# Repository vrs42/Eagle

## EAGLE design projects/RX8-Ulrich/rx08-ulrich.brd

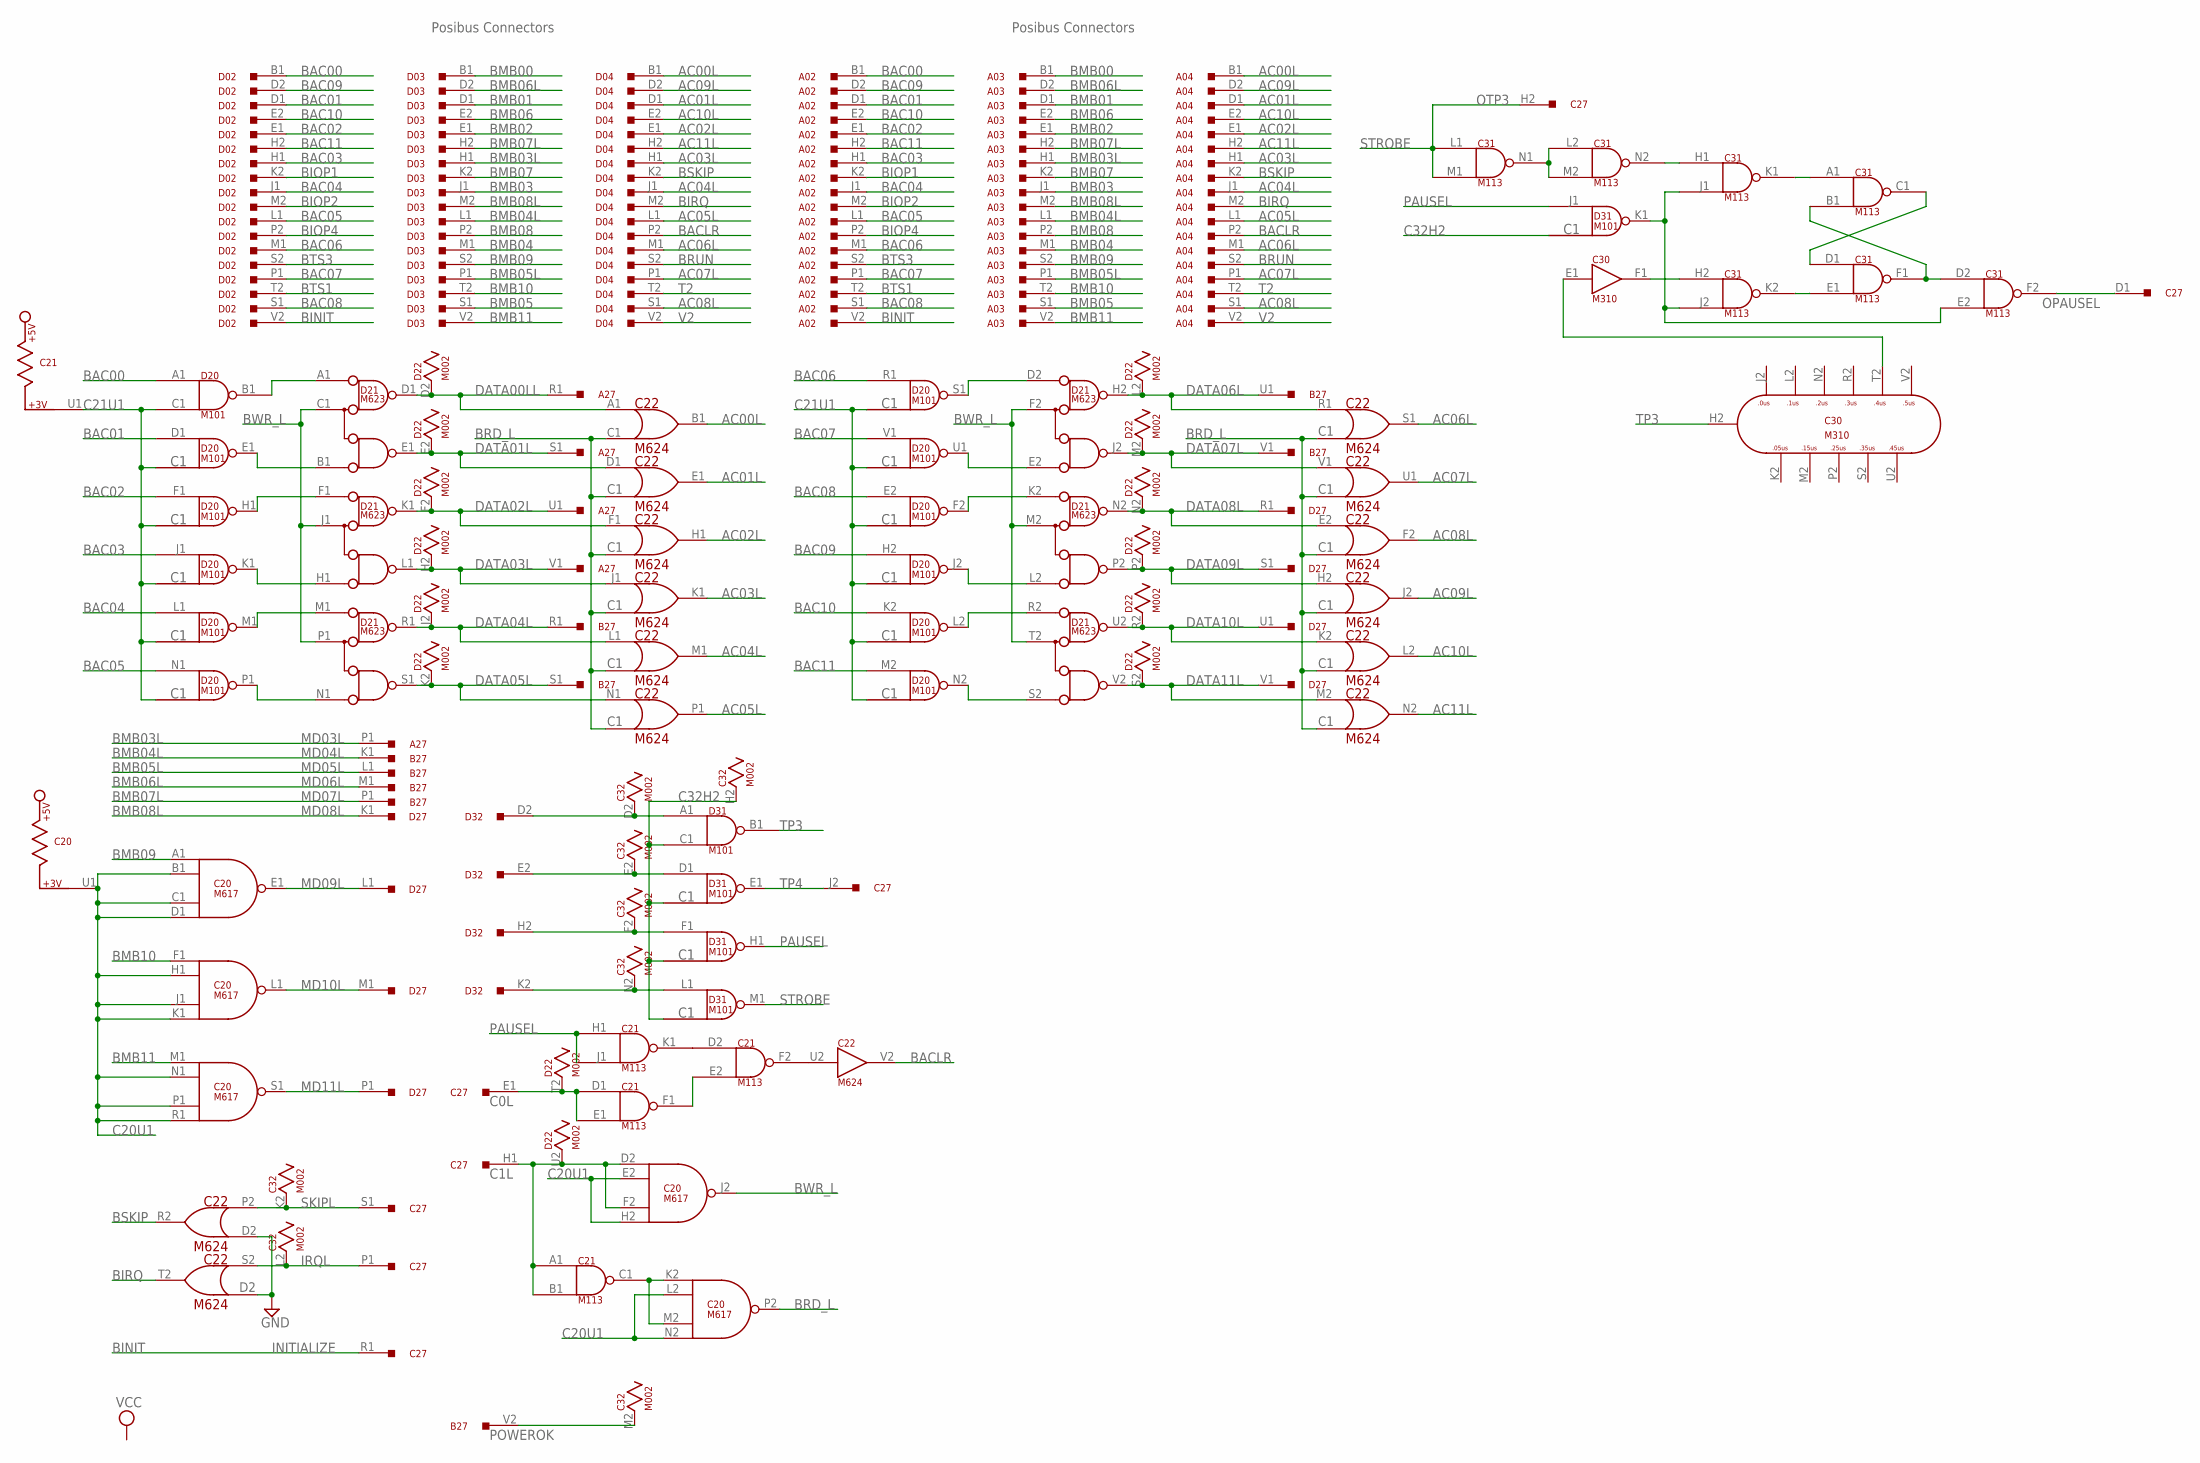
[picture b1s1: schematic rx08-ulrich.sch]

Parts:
A02, A03, A04: M903; H807
A27: M916; H807
B27: M916; H807
C20: M617; H807
C21, C31: M113; H807
C22: M624; H807
C27: M916; H807
C30: M310; H807
C32: M002; H807
D02, D03, D04, D32: M903; H807
D20, D31: M101; H807
D21: M623; H807
D22: M002; H807
D27: M916; H807

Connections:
AC00L: A04.B1, C22.B1 (OUT), D04.B1
AC01L: A04.D1, C22.E1 (OUT), D04.D1
AC02L: A04.E1, C22.H1 (OUT), D04.E1
AC03L: A04.H1, C22.K1 (OUT), D04.H1
AC04L: A04.J1, C22.M1 (OUT), D04.J1
AC05L: A04.L1, C22.P1 (OUT), D04.L1
AC06L: A04.M1, C22.S1 (OUT), D04.M1
AC07L: A04.P1, C22.U1 (OUT), D04.P1
AC08L: A04.S1, C22.F2 (OUT), D04.S1
AC09L: A04.D2, C22.J2 (OUT), D04.D2
AC10L: A04.E2, C22.L2 (OUT), D04.E2
AC11L: A04.H2, C22.N2 (OUT), D04.H2
BAC00: A02.B1, D02.B1, D20.A1 (IN1)
BAC01: A02.D1, D02.D1, D20.D1 (IN)
BAC02: A02.E1, D02.E1, D20.F1 (IN)
BAC03: A02.H1, D02.H1, D20.J1 (IN)
BAC04: A02.J1, D02.J1, D20.L1 (IN)
BAC05: A02.L1, D02.L1, D20.N1 (IN)
BAC06: A02.M1, D02.M1, D20.R1 (IN)
BAC07: A02.P1, D02.P1, D20.V1 (IN)
BAC08: A02.S1, D02.S1, D20.E2 (IN)
BAC09: A02.D2, D02.D2, D20.H2 (IN)
BAC10: A02.E2, D02.E2, D20.K2 (IN)
BAC11: A02.H2, D02.H2, D20.M2 (IN)
BACLR: A04.P2, C22.V2 (OUT), D04.P2
BINIT: A02.V2, C27.R1, D02.V2
BIOP1: A02.K2, D02.K2
BIOP2: A02.M2, D02.M2
BIOP4: A02.P2, D02.P2
BIRQ: A04.M2, C22.T2 (OUT), D04.M2
BMB00: A03.B1, D03.B1
BMB01: A03.D1, D03.D1
BMB02: A03.E1, D03.E1
BMB03: A03.J1, D03.J1
BMB03L: A03.H1, A27.P1, D03.H1
BMB04: A03.M1, D03.M1
BMB04L: A03.L1, B27.K1, D03.L1
BMB05: A03.S1, D03.S1
BMB05L: A03.P1, B27.L1, D03.P1
BMB06: A03.E2, D03.E2
BMB06L: A03.D2, B27.M1, D03.D2
BMB07: A03.K2, D03.K2
BMB07L: A03.H2, B27.P1, D03.H2
BMB08: A03.P2, D03.P2
BMB08L: A03.M2, D03.M2, D27.K1
BMB09: A03.S2, C20.A1 (IN1), D03.S2
BMB10: A03.T2, C20.F1 (IN1), D03.T2
BMB11: A03.V2, C20.M1 (IN1), D03.V2
BRD_L: C20.P2 (OUT), C22.C1 (IN2)
BRUN: A04.S2, D04.S2
BSKIP: A04.K2, C22.R2 (OUT), D04.K2
BTS1: A02.T2, D02.T2
BTS3: A02.S2, D02.S2
BWR_L: C20.J2 (OUT), D21.C1 (C), D21.F2 (C), D21.J1 (C), D21.M2 (C), D21.P1 (C), D21.T2 (C)
C0L: C21.D1 (IN1), C21.E1 (IN2), C27.E1, D22.T2
C1L: C20.D2 (IN1), C20.F2 (IN3), C21.A1 (IN1), C21.B1 (IN2), C27.H1, D22.U2
C20U1: C20.B1 (IN2), C20.C1 (IN3), C20.D1 (IN4), C20.E2 (IN2), C20.H1 (IN2), C20.H2 (IN4), C20.J1 (IN3), C20.K1 (IN4), C20.L2 (IN2), C20.N1 (IN2), C20.N2 (IN4), C20.P1 (IN3), C20.R1 (IN4), C20.U1
C21U1: C21.U1, D20.C1 (IN2)
C32H2: C32.H2, D31.C1 (IN2)
DATA00LL: A27.R1, C22.A1 (IN1), D21.D1 (D), D22.D2
DATA01L: A27.S1, C22.D1 (IN), D21.E1 (E), D22.E2
DATA02L: A27.U1, C22.F1 (IN), D21.K1 (D), D22.F2
DATA03L: A27.V1, C22.J1 (IN), D21.L1 (E), D22.H2
DATA04L: B27.R1, C22.L1 (IN), D21.R1 (D), D22.J2
DATA05L: B27.S1, C22.N1 (IN), D21.S1 (E), D22.K2
DATA06L: B27.U1, C22.R1 (IN), D21.H2 (D), D22.L2
DATA07L: B27.V1, C22.V1 (IN), D21.J2 (E), D22.M2
DATA08L: C22.E2 (IN), D21.N2 (D), D22.N2, D27.R1
DATA09L: C22.H2 (IN), D21.P2 (E), D22.P2, D27.S1
DATA10L: C22.K2 (IN), D21.U2 (D), D22.R2, D27.U1
DATA11L: C22.M2 (IN), D21.V2 (E), D22.S2, D27.V1
GND: A02.A1 (GND), A02.C1 (GND), A02.C2 (GND), A02.F1 (GND), A02.F2 (GND), A02.J2 (GND), A02.K1 (GND), A02.L2 (GND), A02.N1 (GND), A02.N2 (GND), A02.R1 (GND), A02.R2 (GND), A02.T1 (GND), A02.U2 (GND), A03.A1 (GND), A03.C1 (GND), A03.C2 (GND), A03.F1 (GND), A03.F2 (GND), A03.J2 (GND), A03.K1 (GND), A03.L2 (GND), A03.N1 (GND), A03.N2 (GND), A03.R1 (GND), A03.R2 (GND), A03.T1 (GND), A03.U2 (GND), A04.A1 (GND), A04.C1 (GND), A04.C2 (GND), A04.F1 (GND), A04.F2 (GND), A04.J2 (GND), A04.K1 (GND), A04.L2 (GND), A04.N1 (GND), A04.N2 (GND), A04.R1 (GND), A04.R2 (GND), A04.T1 (GND), A04.U2 (GND), C20.C2 (GND), C20.T1 (GND), C21.C2 (GND), C21.T1 (GND), C22.C2 (GND), C22.D2 (IN2), C22.T1 (GND), C30.C2 (GND), C30.T1 (GND), C31.C2 (GND), C31.T1 (GND), C32.C2 (GND), D02.A1 (GND), D02.C1 (GND), D02.C2 (GND), D02.F1 (GND), D02.F2 (GND), D02.J2 (GND), D02.K1 (GND), D02.L2 (GND), D02.N1 (GND), D02.N2 (GND), D02.R1 (GND), D02.R2 (GND), D02.T1 (GND), D02.U2 (GND), D03.A1 (GND), D03.C1 (GND), D03.C2 (GND), D03.F1 (GND), D03.F2 (GND), D03.J2 (GND), D03.K1 (GND), D03.L2 (GND), D03.N1 (GND), D03.N2 (GND), D03.R1 (GND), D03.R2 (GND), D03.T1 (GND), D03.U2 (GND), D04.A1 (GND), D04.C1 (GND), D04.C2 (GND), D04.F1 (GND), D04.F2 (GND), D04.J2 (GND), D04.K1 (GND), D04.L2 (GND), D04.N1 (GND), D04.N2 (GND), D04.R1 (GND), D04.R2 (GND), D04.T1 (GND), D04.U2 (GND), D20.C2 (GND), D20.T1 (GND), D21.C2 (GND), D21.T1 (GND), D21.U1 (GND), D21.V1 (GND), D22.C2 (GND), D31.C2 (GND), D31.T1 (GND), D32.A1 (GND), D32.C1 (GND), D32.C2 (GND), D32.F1 (GND), D32.F2 (GND), D32.J2 (GND), D32.K1 (GND), D32.L2 (GND), D32.N1 (GND), D32.N2 (GND), D32.R1 (GND), D32.R2 (GND), D32.T1 (GND), D32.U2 (GND)
IRQL: C22.S2 (IN), C27.P1, C32.L2
MD09L: C20.E1 (OUT), D27.L1
MD10L: C20.L1 (OUT), D27.M1
MD11L: C20.S1 (OUT), D27.P1
unnamed: D20.B1 (OUT), D21.A1 (A)
unnamed: D20.E1 (OUT), D21.B1 (B)
unnamed: D20.H1 (OUT), D21.F1 (A)
unnamed: D20.K1 (OUT), D21.H1 (B)
unnamed: D20.P1 (OUT), D21.N1 (B)
unnamed: D20.M1 (OUT), D21.M1 (A)
unnamed: C20.K2 (IN1), C20.M2 (IN3), C21.C1 (OUT)
unnamed: D20.N2 (OUT), D21.S2 (B)
unnamed: C32.D2, D31.A1 (IN1), D32.D2
unnamed: D20.J2 (OUT), D21.L2 (B)
unnamed: D20.U1 (OUT), D21.E2 (B)
unnamed: D20.S1 (OUT), D21.D2 (A)
unnamed: D20.F2 (OUT), D21.K2 (A)
unnamed: D20.L2 (OUT), D21.R2 (A)
unnamed: C32.E2, D31.D1 (IN), D32.E2
unnamed: C32.F2, D31.F1 (IN), D32.H2
unnamed: C32.N2, D31.L1 (IN), D32.K2
unnamed: C31.E2 (IN2), C31.J1 (IN2), C31.J2 (IN2), D31.K1 (OUT)
unnamed: C21.E2 (IN2), C21.F1 (OUT)
unnamed: C21.D2 (IN1), C21.K1 (OUT)
unnamed: C31.C1 (OUT), C31.D1 (IN1)
unnamed: C31.B1 (IN2), C31.D2 (IN1), C31.F1 (OUT)
unnamed: C21.F2 (OUT), C22.U2 (IN)
unnamed: C30.E1 (IN), C30.T2
unnamed: C30.F1 (OUT), C31.H2 (IN1)
unnamed: C31.L2 (IN1), C31.M2 (IN2), C31.N1 (OUT)
unnamed: C31.H1 (IN1), C31.N2 (OUT)
unnamed: C31.A1 (IN1), C31.K1 (OUT)
unnamed: C31.E1 (IN2), C31.K2 (OUT)
OPAUSEL: C27.D1, C31.F2 (OUT)
PAUSEL: C21.H1 (IN1), C21.J1 (IN2), D31.H1 (OUT), D31.J1 (IN)
POWEROK: B27.V2, C32.M2
SKIPL: C22.P2 (IN1), C27.S1, C32.K2
STROBE: C27.H2, C31.L1 (IN1), C31.M1 (IN2), D31.M1 (OUT)
T2: A04.T2, D04.T2
TP3: C30.H2, D31.B1 (OUT)
TP4: C27.J2, D31.E1 (OUT)
V2: A04.V2, D04.V2
VCC: C20.A2 (VCC), C21.A2 (VCC), C22.A2 (VCC), C30.A2 (VCC), C31.A2 (VCC), C32.A2 (VCC), D20.A2 (VCC), D21.A2 (VCC), D22.A2 (VCC), D31.A2 (VCC)

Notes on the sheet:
Posibus Connectors
MD03L
MD04L
MD05L
MD06L
MD07L
MD08L
INITIALIZE
OTP3

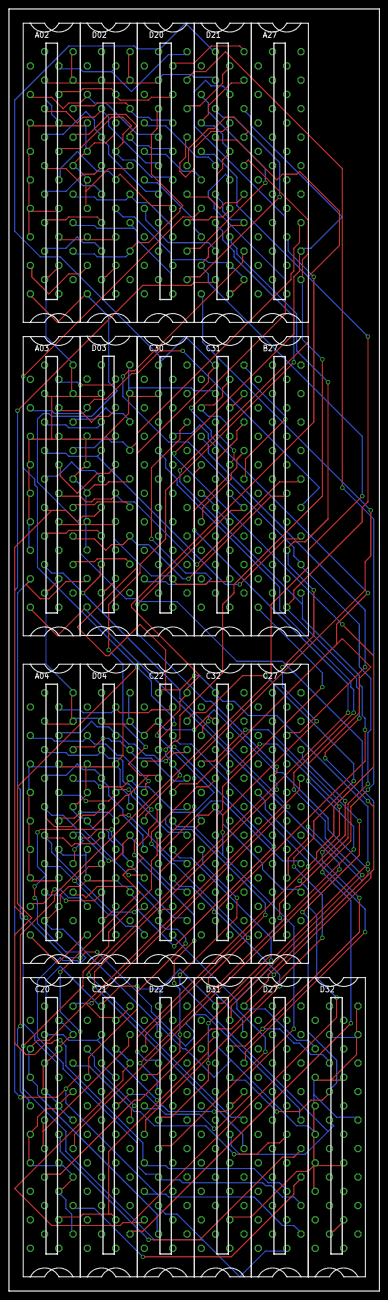
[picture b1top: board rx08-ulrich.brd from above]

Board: 2 copper layers, 82.5 x 285.8 mm, 21 parts (0 on the bottom side), 115 nets.

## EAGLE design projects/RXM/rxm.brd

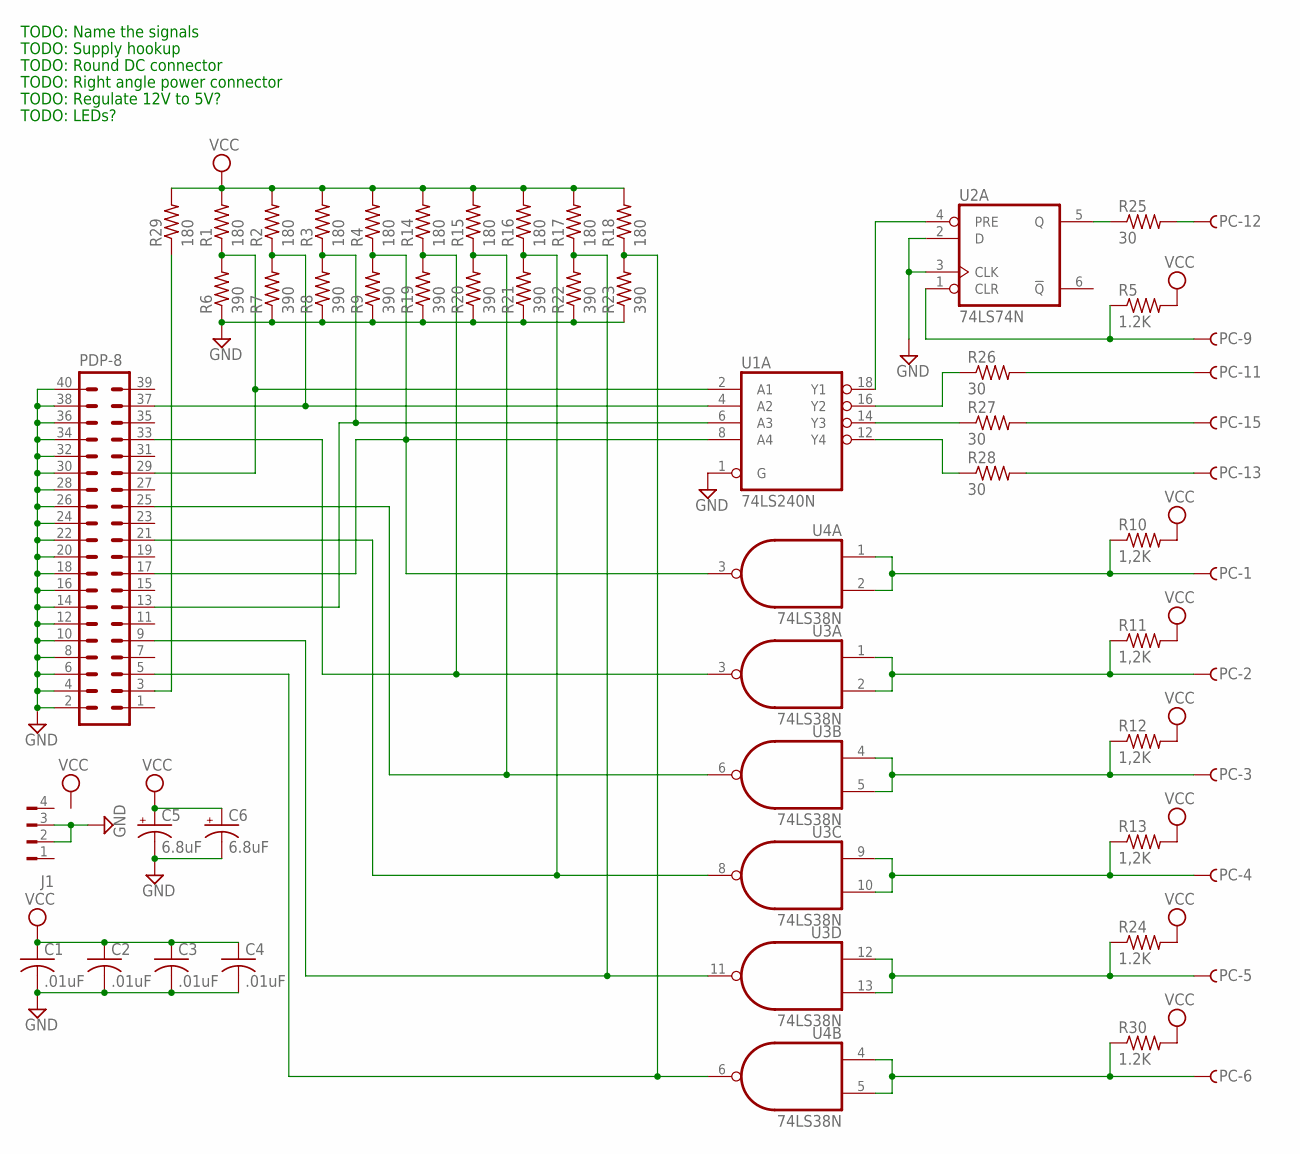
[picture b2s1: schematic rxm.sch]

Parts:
C1, C2, C3, C4: .01uF; C050-025X075
C5, C6: 6.8uF; E2,5-6E
J1: FLOPPY-4
PC: F25HS; F25H
PDP-8: 40H
R1, R2, R3, R4, R14, R15, R16, R17, R18, R29: 180; 0207/10
R5, R24, R30: 1.2K; 0207/10
R6, R7, R8, R9, R19, R20, R21, R22, R23: 390; 0207/10
R10, R11, R12, R13: 1,2K; 0207/10
R25, R26, R27, R28: 30; 0207/10
U1: 74LS240N; DIL20
U2: 74LS74N; DIL14
U3, U4: 74LS38N; DIL14

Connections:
GND: C1.2, C2.2, C3.2, C4.2, C5.-, C6.-, J1.2, J1.3, PDP-8.2, PDP-8.4, PDP-8.6, PDP-8.8, PDP-8.10, PDP-8.12, PDP-8.14, PDP-8.16, PDP-8.18, PDP-8.20, PDP-8.22, PDP-8.24, PDP-8.26, PDP-8.28, PDP-8.30, PDP-8.32, PDP-8.34, PDP-8.36, PDP-8.38, PDP-8.40, R6.1, R7.1, R8.1, R9.1, R19.1, R20.1, R21.1, R22.1, R23.1, U1.1 (G), U1.10 (GND), U2.2 (D), U2.3 (CLK), U2.7 (GND), U3.7 (GND), U4.7 (GND)
unnamed: PDP-8.29, R1.1, R6.2, U1.2 (A1)
unnamed: PDP-8.37, R2.1, R7.2, U1.4 (A2)
unnamed: PDP-8.13, R3.1, R8.2, U1.6 (A3)
unnamed: PDP-8.17, R4.1, R9.2, U1.8 (A4), U4.3 (O)
unnamed: PDP-8.33, R14.1, R19.2, U3.3 (O)
unnamed: PDP-8.25, R15.1, R20.2, U3.6 (O)
unnamed: PDP-8.21, R16.1, R21.2, U3.8 (O)
unnamed: PDP-8.9, R17.1, R22.2, U3.11 (O)
unnamed: PDP-8.5, R18.1, R23.2, U4.6 (O)
unnamed: PC.12, R25.2
unnamed: PC.11, R26.2
unnamed: PC.15, R27.2
unnamed: PC.13, R28.2
unnamed: PDP-8.3, R29.1
unnamed: PC.1, R10.1, U4.1 (I0), U4.2 (I1)
unnamed: PC.2, R11.1, U3.1 (I0), U3.2 (I1)
unnamed: PC.3, R12.1, U3.4 (I0), U3.5 (I1)
unnamed: PC.4, R13.1, U3.9 (I0), U3.10 (I1)
unnamed: PC.6, R30.1, U4.4 (I0), U4.5 (I1)
unnamed: PC.5, R24.1, U3.12 (I0), U3.13 (I1)
unnamed: U1.18 (Y1), U2.4 (PRE)
unnamed: PC.9, R5.1, U2.1 (CLR)
unnamed: R25.1, U2.5 (Q)
unnamed: R28.1, U1.12 (Y4)
unnamed: R27.1, U1.14 (Y3)
unnamed: R26.1, U1.16 (Y2)
VCC: C1.1, C2.1, C3.1, C4.1, C5.+, C6.+, R1.2, R2.2, R3.2, R4.2, R5.2, R10.2, R11.2, R12.2, R13.2, R14.2, R15.2, R16.2, R17.2, R18.2, R24.2, R29.2, R30.2, U1.20 (VCC), U2.14 (VCC), U3.14 (VCC), U4.14 (VCC)

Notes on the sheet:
TODO: Supply hookup
TODO: Round DC connector
TODO: Right angle power connector
TODO: Regulate 12V to 5V?
TODO: Name the signals
TODO: LEDs?

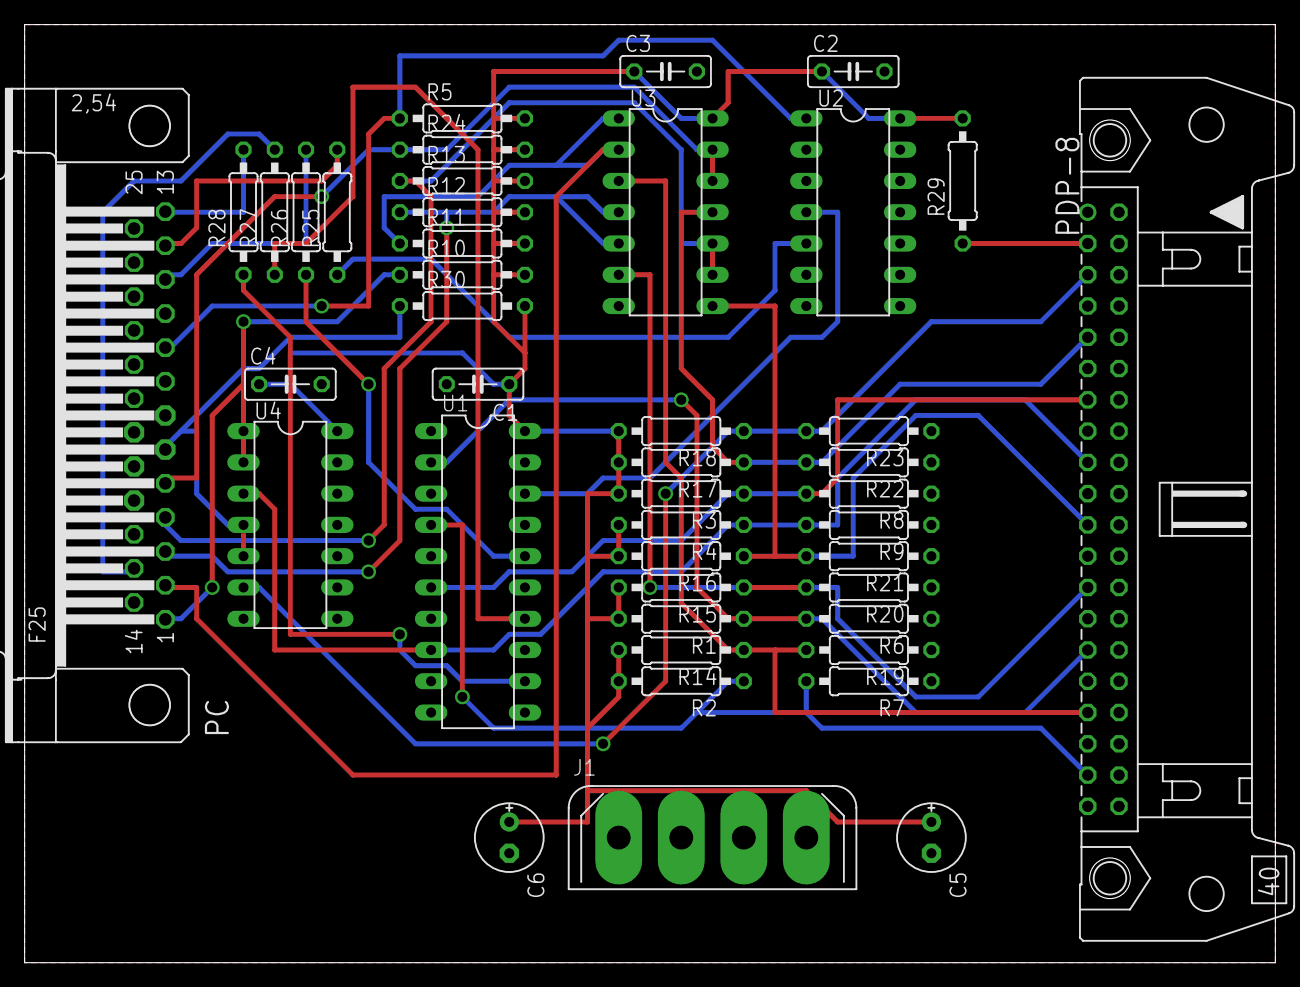
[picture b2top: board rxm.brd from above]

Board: 2 copper layers, 101.6 x 76.2 mm, 43 parts (0 on the bottom side), 28 nets.

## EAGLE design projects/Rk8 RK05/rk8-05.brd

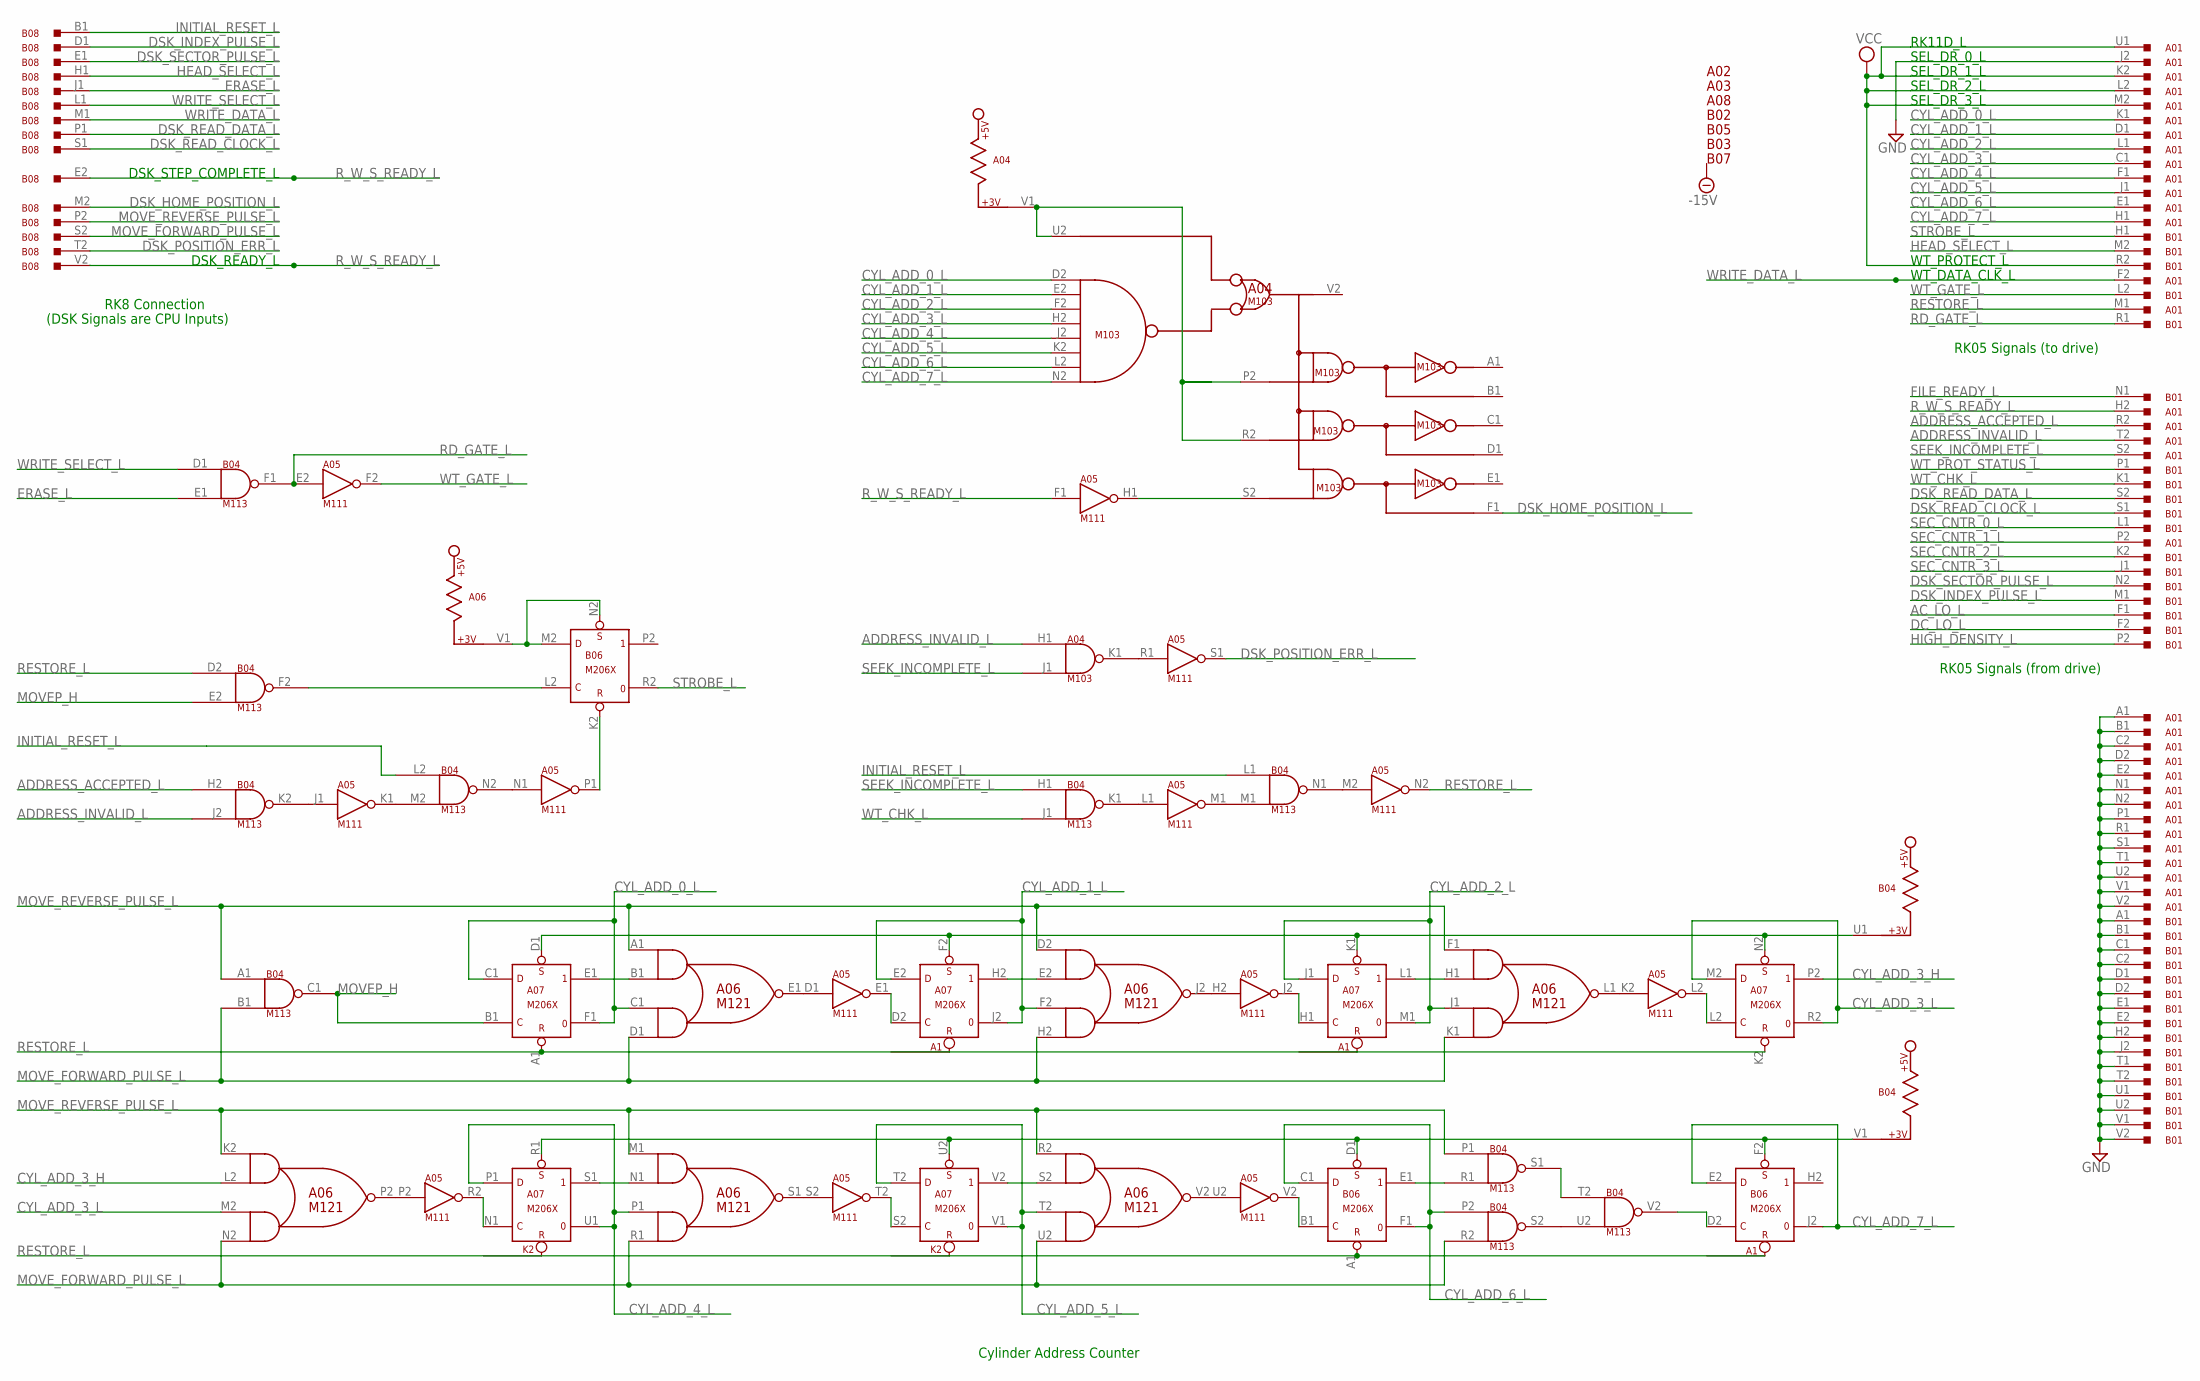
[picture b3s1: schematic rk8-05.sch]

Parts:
A01: M916; H807
A02, A03, A08: EMPTY; H807
A04: M103; H807
A05: M111; H807
A06: M121; H807
A07: M206X; H807
B01: M916; H807
B02, B03, B05, B07: EMPTY; H807
B04: M113; H807
B06: M206X; H807
B08: M903; H807

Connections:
-15V: A02.B2 (-15V), A03.B2 (-15V), A08.B2 (-15V), B02.B2 (-15V), B03.B2 (-15V), B05.B2 (-15V), B07.B2 (-15V)
AC_LO_L: B01.F1
ADDRESS_ACCEPTED_L: A01.R2, B04.H2 (IN1)
ADDRESS_INVALID_L: A01.T2, A04.H1 (IN1), B04.J2 (IN2)
CYL_ADD_0_L: A01.K1, A04.D2, A06.C1 (IN2A), A07.C1 (D), A07.F1 (0)
CYL_ADD_1_L: A01.D1, A04.E2, A06.F2 (IN2A), A07.E2 (D), A07.J2 (0)
CYL_ADD_2_L: A01.L1, A04.F2, A06.J1 (IN2A), A07.J1 (D), A07.M1 (0)
CYL_ADD_3_H: A06.L2 (IN1B), A07.P2 (1)
CYL_ADD_3_L: A01.C1, A04.H2, A06.M2 (IN2A), A07.M2 (D), A07.R2 (0)
CYL_ADD_4_L: A01.F1, A04.J2, A06.P1 (IN2A), A07.P1 (D), A07.U1 (0)
CYL_ADD_5_L: A01.J1, A04.K2, A06.T2 (IN2A), A07.T2 (D), A07.V1 (0)
CYL_ADD_6_L: A01.E1, A04.L2, B04.P2 (IN1), B06.C1 (D), B06.F1 (0)
CYL_ADD_7_L: A01.H1, A04.N2, B06.E2 (D), B06.J2 (0)
DC_LO_L: B01.F2
DSK_HOME_POSITION_L: A04.F1, B08.M2
DSK_INDEX_PULSE_L: B01.M1, B08.D1
DSK_POSITION_ERR_L: A05.S1 (OUT), B08.T2
DSK_READ_CLOCK_L: B01.S1, B08.S1
DSK_READ_DATA_L: B01.S2, B08.P1
DSK_SECTOR_PULSE_L: B01.N2, B08.E1
ERASE_L: B04.E1 (IN2), B08.J1
FILE_READY_L: B01.N1
GND: A01.A1, A01.B1, A01.C2, A01.D2, A01.E2, A01.J2, A01.N1, A01.N2, A01.P1, A01.R1, A01.S1, A01.T1, A01.U2, A01.V1, A01.V2, A02.C2 (GND), A03.C2 (GND), A04.C2 (GND), A04.T1 (GND), A05.C2 (GND), A05.T1 (GND), A06.C2 (GND), A06.T1 (GND), A07.C2 (GND), A07.T1 (GND), A08.C2 (GND), B01.A1, B01.B1, B01.C1, B01.C2, B01.D1, B01.D2, B01.E1, B01.E2, B01.H2, B01.J2, B01.T1, B01.T2, B01.U1, B01.U2, B01.V1, B01.V2, B02.C2 (GND), B03.C2 (GND), B04.C2 (GND), B04.T1 (GND), B05.C2 (GND), B06.C2 (GND), B06.T1 (GND), B07.C2 (GND), B08.A1 (GND), B08.C1 (GND), B08.C2 (GND), B08.F1 (GND), B08.F2 (GND), B08.J2 (GND), B08.K1 (GND), B08.L2 (GND), B08.N1 (GND), B08.N2 (GND), B08.R1 (GND), B08.R2 (GND), B08.T1 (GND), B08.U2 (GND)
HEAD_SELECT_L: B01.M2, B08.H1
HIGH_DENSITY_L: B01.P2
INITIAL_RESET_L: B04.L1 (IN1), B04.L2 (IN1), B08.B1
MOVEP_H: A07.B1 (C), B04.C1 (OUT), B04.E2 (IN2)
MOVE_FORWARD_PULSE_L: A06.D1 (IN2B), A06.H2 (IN2B), A06.K1 (IN2B), A06.N2 (IN2B), A06.R1 (IN2B), A06.U2 (IN2B), B04.B1 (IN2), B04.R2 (IN2), B08.S2
MOVE_REVERSE_PULSE_L: A06.A1 (IN1A), A06.D2 (IN1A), A06.F1 (IN1A), A06.K2 (IN1A), A06.M1 (IN1A), A06.R2 (IN1A), B04.A1 (IN1), B04.P1 (IN1), B08.P2
unnamed: A05.P2 (IN), A06.P2 (OUT)
unnamed: A07.D1 (S), A07.F2 (S), A07.K1 (S), A07.N2 (S), B04.U1
unnamed: A07.R1 (S), A07.U2 (S), B04.V1, B06.D1 (S), B06.F2 (S)
unnamed: A06.B1 (IN1B), A07.E1 (1)
unnamed: A05.E1 (OUT), A07.D2 (C)
unnamed: A06.E2 (IN1B), A07.H2 (1)
unnamed: A05.J2 (OUT), A07.H1 (C)
unnamed: A05.R2 (OUT), A07.N1 (C)
unnamed: A06.H1 (IN1B), A07.L1 (1)
unnamed: A05.S2 (IN), A06.S1 (OUT)
unnamed: A05.L2 (OUT), A07.L2 (C)
unnamed: A05.T2 (OUT), A07.S2 (C)
unnamed: B04.S2 (OUT), B04.U2 (IN2)
unnamed: B04.S1 (OUT), B04.T2 (IN1)
unnamed: A05.H2 (IN), A06.J2 (OUT)
unnamed: A04.S2, A05.H1 (OUT)
unnamed: A05.D1 (IN), A06.E1 (OUT)
unnamed: A05.U2 (IN), A06.V2 (OUT)
unnamed: B04.V2 (OUT), B06.D2 (C)
unnamed: B04.R1 (IN2), B06.E1 (1)
unnamed: A05.K2 (IN), A06.L1 (OUT)
unnamed: A06.S2 (IN1B), A07.V2 (1)
unnamed: A06.N1 (IN1B), A07.S1 (1)
unnamed: B04.F2 (OUT), B06.L2 (C)
unnamed: A05.L1 (IN), B04.K1 (OUT)
unnamed: A05.M1 (OUT), B04.M1 (IN2)
unnamed: A06.V1, B06.M2 (D), B06.N2 (S)
unnamed: A04.K1 (OUT), A05.R1 (IN)
unnamed: A05.V2 (OUT), B06.B1 (C)
unnamed: A05.J1 (IN), B04.K2 (OUT)
unnamed: A05.K1 (OUT), B04.M2 (IN2)
unnamed: A05.N1 (IN), B04.N2 (OUT)
unnamed: A05.P1 (OUT), B06.K2 (R)
unnamed: A05.M2 (IN), B04.N1 (OUT)
unnamed: A04.P2, A04.R2, A04.U2, A04.V1
RD_GATE_L: A05.E2 (IN), B01.R1, B04.F1 (OUT)
RESTORE_L: A01.M1, A05.N2 (OUT), A07.A1 (R), A07.K2 (R), B04.D2 (IN1), B06.A1 (R)
R_W_S_READY_L: A01.H2, A05.F1 (IN), B08.E2, B08.V2
SEC_CNTR_0_L: B01.L1
SEC_CNTR_1_L: A01.P2
SEC_CNTR_2_L: B01.K2
SEC_CNTR_3_L: B01.J1
SEEK_INCOMPLETE_L: A01.S2, A04.J1 (IN2), B04.H1 (IN1)
STROBE_L: B01.H1, B06.R2 (0)
VCC: A01.K2, A01.L2, A01.M2, A01.U1, A02.A2 (VCC), A03.A2 (VCC), A04.A2 (VCC), A05.A2 (VCC), A06.A2 (VCC), A07.A2 (VCC), A08.A2 (VCC), B01.R2, B02.A2 (VCC), B03.A2 (VCC), B04.A2 (VCC), B05.A2 (VCC), B06.A2 (VCC), B07.A2 (VCC)
WRITE_DATA_L: A01.F2, B08.M1
WRITE_SELECT_L: B04.D1 (IN1), B08.L1
WT_CHK_L: B01.K1, B04.J1 (IN2)
WT_GATE_L: A05.F2 (OUT), B01.L2
WT_PROT_STATUS_L: B01.P1

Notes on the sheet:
RK8 Connection
(DSK Signals are CPU Inputs)
RK05 Signals (to drive)
RK05 Signals (from drive)
Cylinder Address Counter
SEL_DR_0_L
SEL_DR_1_L
SEL_DR_2_L
SEL_DR_3_L
RK11D_L
WT_PROTECT_L
WT_DATA_CLK_L
DSK_STEP_COMPLETE_L
DSK_READY_L

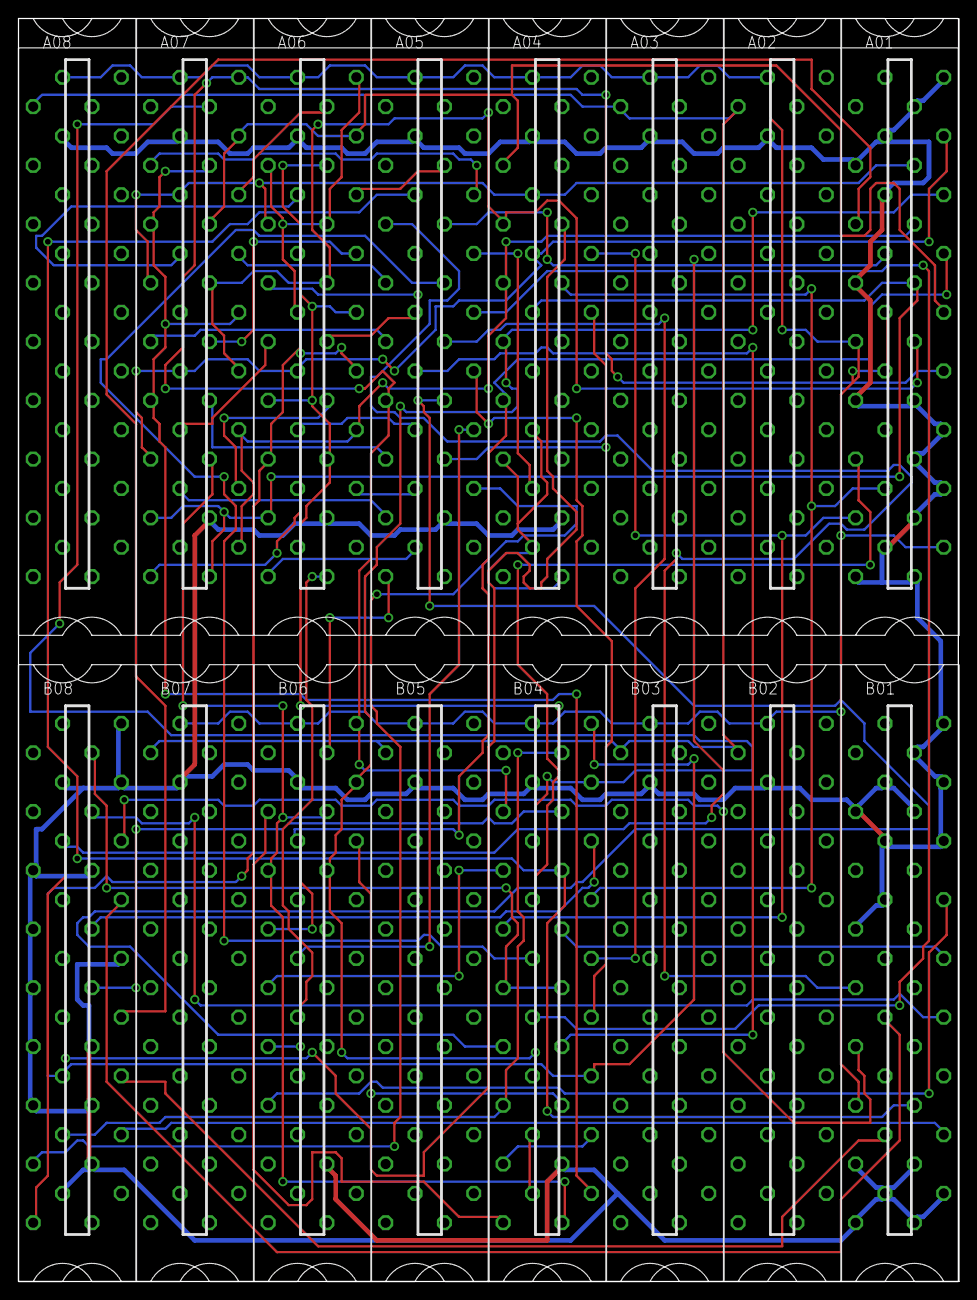
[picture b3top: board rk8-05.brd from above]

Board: 2 copper layers, 101.6 x 136.5 mm, 18 parts (0 on the bottom side), 70 nets.

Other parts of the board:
U$1, U$2: CBLOCK

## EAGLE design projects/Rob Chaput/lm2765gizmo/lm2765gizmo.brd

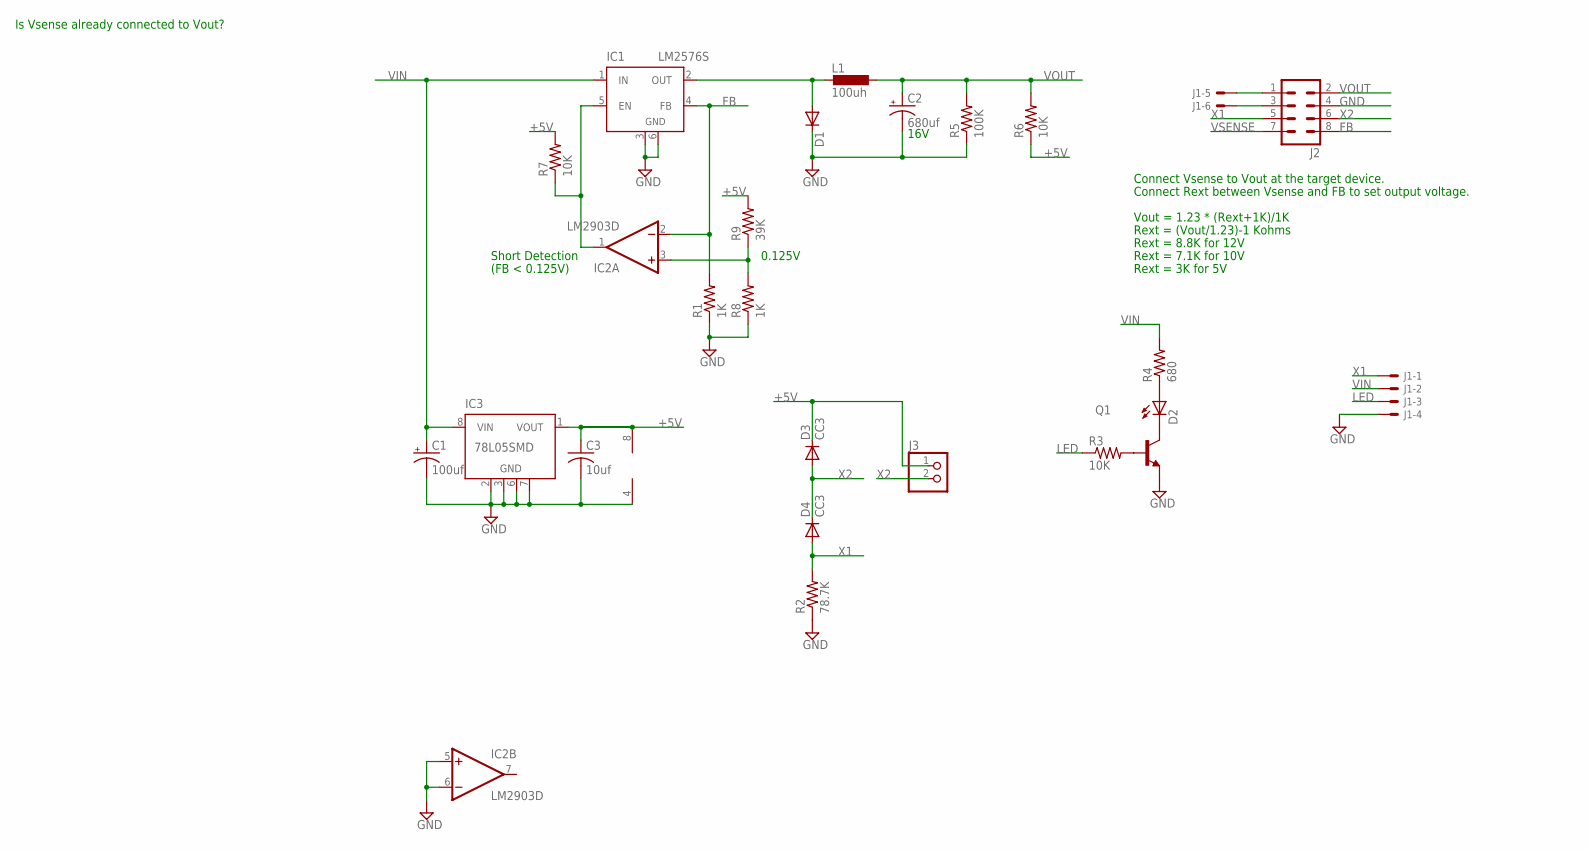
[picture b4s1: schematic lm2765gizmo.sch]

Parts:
C1: 100uf; 140CLH-0810
C2: 680uf; 140CLH-1014
C3: 10uf; C0805
D1: DIODE-SMC; SMC
D2: LEDCHIP-LED0805; CHIP-LED0805
D3, D4: CC3; SOD80C
IC1: LM2576S; TO263-5
IC2: LM2903D; SO08
IC3: 78L05SMD; SO08
J1: 53261-06
J2: MA04-2
J3: PINHD-1X2; 1X02
L1: 100uh; DO3316P
Q1: BC808-NPN-SOT23-BEC; SOT23-BEC
R1, R8: 1K; M0805
R2: 78.7K; M0805
R3, R6, R7: 10K; M0805
R4: 680; M0805
R5: 100K; M0805
R9: 39K; M0805

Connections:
+5V: C3.1, D3.C, IC2.8 (V+), IC3.1 (VOUT), J3.1, R6.1, R7.2, R9.2
FB: IC1.4 (FB), IC2.2 (-IN), J2.8, R1.2
GND: C1.-, C2.-, C3.2, D1.C, IC1.3 (GND), IC1.6 (GND), IC2.4 (V-), IC2.5 (+IN), IC2.6 (-IN), IC3.2 (GND), IC3.3 (GND), IC3.6 (GND), IC3.7 (GND), J1.4, J2.4, Q1.E, R1.1, R2.1, R5.1, R8.1
LED: J1.3, R3.1
unnamed: IC1.5 (EN), IC2.1 (OUT), R7.1
unnamed: IC2.3 (+IN), R8.2, R9.1
unnamed: D1.A, IC1.2 (OUT), L1.1
unnamed: D2.A, R4.1
unnamed: D2.C, Q1.C
unnamed: Q1.B, R3.2
unnamed: J1.5, J2.1
unnamed: J1.6, J2.3
VIN: C1.+, IC1.1 (IN), IC3.8 (VIN), J1.2, R4.2
VOUT: C2.+, J2.2, L1.2, R5.2, R6.2
VSENSE: J2.7
X1: D4.A, J1.1, J2.5, R2.2
X2: D3.A, D4.C, J2.6, J3.2

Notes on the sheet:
0.125V
Short Detection
(FB < 0.125V)
Connect Rext between Vsense and FB to set output voltage.
Vout = 1.23 * (Rext+1K)/1K
Is Vsense already connected to Vout?
16V
Rext = 7.1K for 10V
Rext = 8.8K for 12V
Rext = 3K for 5V
Rext = (Vout/1.23)-1 Kohms
Connect Vsense to Vout at the target device.

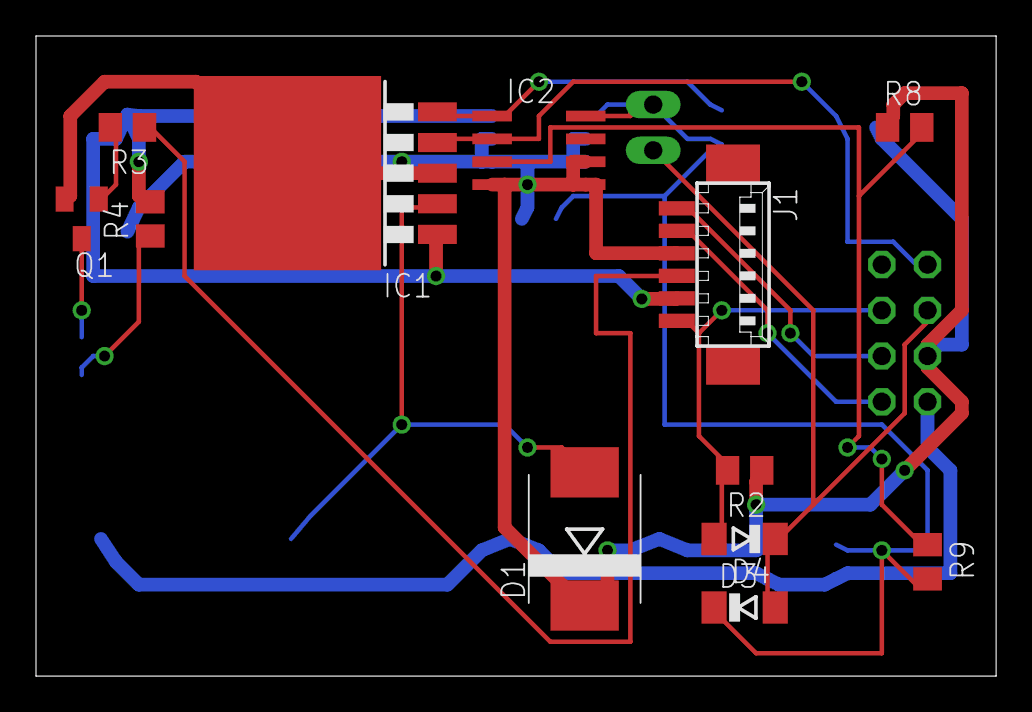
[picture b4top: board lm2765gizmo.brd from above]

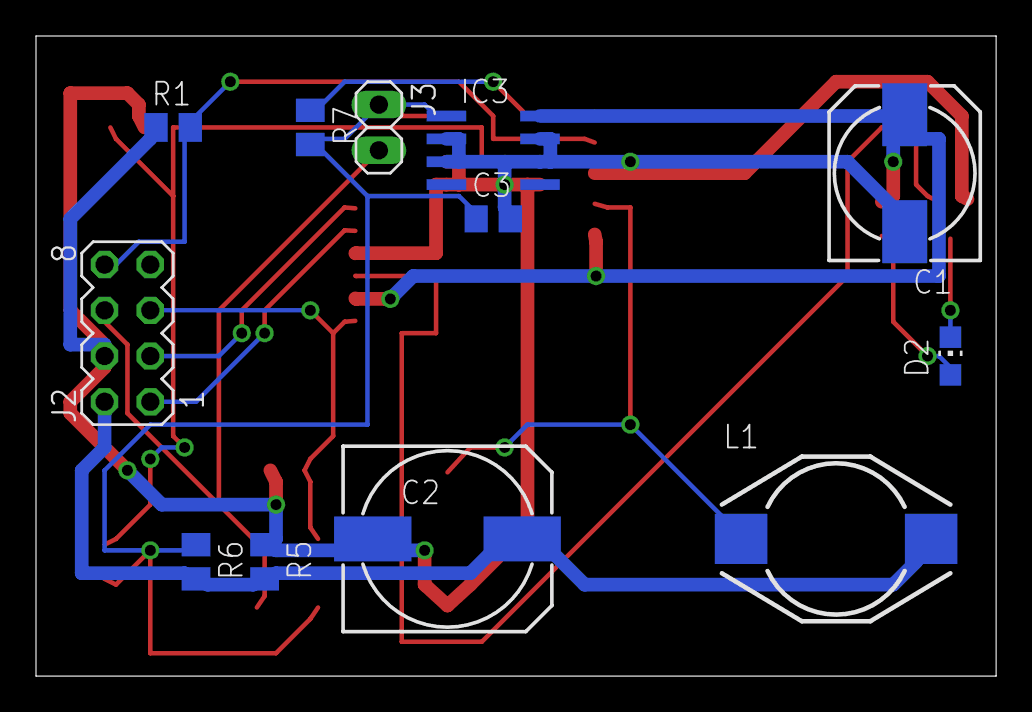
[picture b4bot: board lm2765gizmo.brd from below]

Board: 2 copper layers, 53.3 x 35.6 mm, 24 parts (12 on the bottom side), 16 nets.
